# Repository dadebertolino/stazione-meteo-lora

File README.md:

# Stazione meteo LoRa

Stazione meteo scolastica su rete di sensori **LoRa P2P** con moduli **RAK3172**
(firmware RUI3 ≥ 4.1). I nodi trasmettono le misure direttamente a un
ricevitore, senza rete LoRaWAN e senza gateway; il ricevitore le verifica e le
stampa in CSV su seriale; un Raspberry aggiunge data e ora e le invia al sito
della scuola.

**Autore:** [Davide Bertolino](https://www.davidebertolino.it) ·
**Licenze:** software GPL v2 o successive ([`LICENSE`](LICENSE)), hardware
CERN-OHL-S v2 ([`hardware/LICENSE`](hardware/LICENSE))

Il plugin WordPress che mostra i dati sul sito è in un repository a parte,
[dadebertolino/db-stazione-meteo](https://github.com/dadebertolino/db-stazione-meteo),
perché si aggiorna da solo dalle sue release.

```
nodo BME280 (ID 2) ──┐
                     │  LoRa P2P 868,1 MHz        seriale USB, CSV
nodo SHT45 (ID 1)* ──┴───────────────────► ricevitore ──────────────► PC o Raspberry
                                                                       registratore (prove)
                                                                       bridge ──► sito WordPress*
```

\* non ancora realizzati.

| Componente | Ruolo | Stato |
|---|---|---|
| [`nodo_bme280/`](nodo_bme280/nodo_bme280.ino) | nodo temperatura, umidità, pressione con sensore BME280 | firmware 1.2, in prova |
| [`ricevitore_p2p/`](ricevitore_p2p/ricevitore_p2p.ino) | ricevitore: verifica e decodifica i pacchetti, li stampa in CSV | firmware 1.2, in prova |
| [`registratore/`](registratore/registra.py) | salva la seriale del ricevitore con l'ora di arrivo, per le prove | pronto |
| [`test_banco/`](test_banco/esegui.sh) | prove del formato dei pacchetti sul PC, senza schede | 17 test |
| nodo SHT45 | nodo temperatura e umidità | da scrivere quando arrivano i componenti; il ricevitore ne decodifica già il pacchetto |
| [`bridge/`](bridge/README.md) | sul Raspberry: aggiunge data e ora, coda locale, invio al sito | struttura |
| [`hardware/`](hardware/README.md) | progetti KiCad delle schede: nodo BME280 e ricevitore, libreria condivisa | progetti vuoti, scelte da fare |
| [db-stazione-meteo](https://github.com/dadebertolino/db-stazione-meteo) | plugin WordPress: riceve le misure e le mostra sul sito della scuola (repository a parte) | struttura |

Ogni sketch sta in una cartella con lo stesso nome del file `.ino`, come richiede
l'IDE Arduino. Si compilano con il pacchetto di schede RAKwireless RUI3
(verificati con la versione 4.3.0, scheda *WisDuo RAK3172 Evaluation Board*).

**Nodi e ricevitore vanno aggiornati insieme**: il formato dei pacchetti è
cambiato con il firmware 1.0 e il ricevitore scarta quelli del formato
precedente.

## Parametri radio

Devono essere **identici** su nodi e ricevitore. All'avvio ogni sketch fa
un'autodiagnosi: se il modulo è in modalità LoRaWAN passa a P2P e si riavvia, poi
confronta i parametri salvati in flash e corregge quelli diversi. Se il
passaggio a P2P non riesce lo segnala e prosegue, invece di riavviarsi in
continuazione.

| Parametro | Valore |
|---|---|
| Frequenza | 868,100 MHz |
| Spreading factor | SF7 |
| Banda | 125 kHz |
| Coding rate | 4/5 |
| Preambolo | 8 simboli |
| Potenza | 14 dBm |

### Limiti di banda

Con banda 125 kHz centrata su 868,1 MHz il segnale occupa 868,0375-868,1625 MHz,
tutto dentro la sottobanda **868,0-868,6 MHz** (ERC/REC 70-03), che ammette
**25 mW ERP** e **duty cycle 1 %**: al massimo 36 s di trasmissione per ora.

A SF7 il tempo in aria cresce a gradini di 5 simboli (~5 ms). I pacchetti del
formato v1, 15 byte per il BME280 e 13 per l'SHT45, stanno sullo stesso gradino:
**circa 46 ms**.

| Intervallo | Duty cycle |
|---|---|
| 30 s (prova) | ~0,15 % |
| 10 min (esercizio) | ~0,008 % |

Il nodo non compila con un intervallo sotto i 10 s (`static_assert`): con 46 ms
in aria l'1 % ne richiederebbe almeno 4,6.

Fino all'ottobre 2026 la frequenza era 868,000 MHz: metà del segnale cadeva sotto
868,0 MHz, in una banda con duty cycle 0,1 %, superato con l'intervallo di prova.

I 14 dBm sono misurati all'uscita del modulo; il limite di 25 mW è riferito
alla potenza irradiata (ERP) e quindi include il guadagno dell'antenna. Con
un'antenna a stilo o a dipolo si resta nel limite; con un'antenna di guadagno
superiore a ~2 dBi la potenza va ridotta di conseguenza.

868,1 MHz è anche il primo canale di LoRaWAN. Se nella zona ci sono dispositivi
LoRaWAN possono esserci collisioni, visibili come salti nel contatore.

## Nodo BME280

### Alimentazione

**Due stilo AA alcaline** collegate direttamente al pin 3V3 del modulo, senza
regolatore: il RAK3172 funziona fra 2,0 e 3,6 V, e senza regolatore
la tensione di alimentazione del modulo è quella delle
batterie. Il nodo la misura con il riferimento interno dell'STM32WL (VREFINT),
confrontato con la sua taratura di fabbrica.

`api.system.bat.get()` di RUI3 non va usata: nel core 4.3.0
(`service_battery.c`) legge l'ADC solo sul RAK3172-SiP e sulle basi WisBlock;
sul RAK3172 restituisce sempre 3,0 V, ed è il valore fisso che il nodo
trasmetteva fino al firmware 1.1.

| Stato | Tensione (2 × AA) | Per cella |
|---|---|---|
| Nuove | 3,1-3,2 V | 1,55-1,6 V |
| A metà vita | ~2,5 V | ~1,25 V |
| Quasi scariche | ~2,2-2,3 V | ~1,1-1,15 V |
| Spegnimento del modulo | 2,0 V | 1,0 V |

Non usare stilo al litio (tipo Energizer L91): nuove arrivano a circa 3,6 V, al
limite massimo del modulo.

Il nodo trasmette due tensioni: **a riposo**, prima della trasmissione, e
**sotto carico**, misurata a metà della trasmissione. Con le alcaline la
differenza fra le due è il segnale più chiaro di batterie in esaurimento, e al
freddo cresce anche con batterie ancora buone. La tensione sotto carico è quella
della trasmissione *precedente*: quando la misura, il pacchetto è già partito.

All'avvio l'autodiagnosi confronta la tensione con due soglie e segnala un
errore se ne è fuori (solo su seriale, il nodo prosegue):

| Costante | Valore | Significato |
|---|---|---|
| `VBAT_MIN_MV` | 2300 mV | alcaline quasi scariche |
| `VBAT_MAX_MV` | 3600 mV | massimo del RAK3172: sopra si rischia di danneggiarlo |

### Collegamenti I2C

| BME280 | RAK3172 |
|---|---|
| VCC | 3V3 |
| GND | GND |
| SDA | PA11 |
| SCL | PA12 |

Sui moduli a 6 pin, `CSB` va a 3V3 per selezionare l'I2C; `SDO` sceglie
l'indirizzo (a GND = `0x76`, a 3V3 = `0x77`). Lo sketch li prova entrambi e
riconosce un BMP280 montato per errore (niente umidità).

A batteria conviene un modulo **senza regolatore né traslatori di livello**: di
solito sono quelli a 6 pin. I moduli a 4 pin che li hanno consumano sempre,
anche quando il sensore dorme.

### Ciclo di funzionamento

1. Lettura del sensore in *forced mode* (una misura, poi il sensore torna a
   dormire) e della tensione a riposo.
2. Trasmissione del pacchetto; a metà trasmissione, lettura della tensione sotto
   carico per il pacchetto successivo.
3. Sleep per l'intervallo **±10 %, scelto a caso** a ogni ciclo: due nodi accesi
   insieme con lo stesso intervallo, altrimenti, trasmetterebbero sempre nello
   stesso istante e collidrebbero a ogni ciclo. Il seme del generatore casuale
   viene dall'identificativo unico del modulo (DevEUI).

| Costante | Prova | Esercizio |
|---|---|---|
| `INTERVAL_MS` | `30000UL` (30 s ± 3 s) | `600000UL` (10 min ± 1 min) |
| `NODE_DEBUG` | `1`: stampa su seriale | `0`: nessuna stampa |
| `NODE_ID` | 1-15, diverso per ogni nodo | |

Cambiare l'intervallo non richiede modifiche al ricevitore, che ascolta in
continuo.

### Robustezza

| Guasto | Cosa fa il nodo |
|---|---|
| **Sensore che non risponde**, misura non conclusa entro 100 ms, registri ai valori di reset (sensore riavviato) o valori fuori dal campo del BME280 (−40…85 °C, 300…1100 hPa) | sblocca il bus I2C, reinizializza il sensore e lo rilegge subito; se non va ancora trasmette il pacchetto con le misure **non disponibili** e riprova al ciclo successivo |
| **Bus I2C bloccato** (il sensore tiene SDA basso) | 9 impulsi su SCL e una condizione di STOP, poi riapre il bus |
| **Firmware bloccato** | **watchdog** a 8 s: il nodo si riavvia. Il watchdog continua a contare anche in sleep, quindi lo sleep lungo è diviso in tratti di 5 s con una ricarica fra l'uno e l'altro |
| **Sleep interrotto in anticipo** | il tempo si conta con `millis()`, che in RUI3 avanza anche in sleep: il nodo si riaddormenta invece di trasmettere prima del dovuto |
| **Riavvio** (calo di tensione, watchdog, reset) | il primo pacchetto dopo il riavvio ha contatore 0 e porta la causa del reset |

Un nodo con il sensore guasto continua a trasmettere tensioni e contatore: dal
ricevitore si distingue da un nodo spento, che non trasmette nulla.

## Formato dei pacchetti (v1)

Interi **big endian**. Ogni pacchetto finisce con un **CRC-16/CCITT-FALSE**
(polinomio 0x1021, valore iniziale 0xFFFF, controllo su "123456789" = 0x29B1)
calcolato su tutti i byte precedenti.

| Byte | BME280 (15 byte) | SHT45 (13 byte) |
|---|---|---|
| 0 | versione formato (4 bit alti, = 1) · ID nodo (4 bit bassi, 1-15) | uguale |
| 1 | contatore | uguale |
| 2 | tipo di nodo (4 bit alti: 1 = BME280, 2 = SHT45) · causa del reset (4 bit bassi) | uguale |
| 3-4 | temperatura °C × 100, con segno | uguale |
| 5-6 | umidità % × 100 | uguale |
| 7-8 | pressione hPa × 10 | tensione a riposo, mV |
| 9-10 | tensione a riposo, mV | tensione sotto carico, mV |
| 11-12 | tensione sotto carico (trasmissione precedente), mV | CRC-16 |
| 13-14 | CRC-16 | — |

La pressione è quella **misurata sul posto**, non riportata al livello del mare.

### Perché un CRC nel payload

La radio ha già un CRC hardware, attivo, ma in RUI3 4.3.0 un pacchetto che non
lo supera **arriva lo stesso allo sketch**. Il driver radio tratta separatamente
i due eventi che la radio segnala insieme, "pacchetto ricevuto" ed "errore CRC":

1. il payload corrotto viene consegnato alla callback come valido
   (`Status = LORA_P2P_RXDONE`);
2. la callback viene richiamata con `Status = LORA_P2P_RXERROR`, ma con il
   buffer del pacchetto precedente.

Il ricevitore scarta il secondo richiamo guardando `Status`, il primo con il CRC
del payload. Il CRC scarta anche i pacchetti di altri dispositivi che usano gli
stessi parametri radio. Dedotto dai sorgenti del core (`service_lora_p2p.c`,
`radio.c`, `stm32wlxx_hal_subghz.c`) e **confermato sulla scheda** il
25/10/2026: in circa 2 ore e mezza sono arrivati 11 pacchetti estranei da 24
byte (RSSI ~−110 dBm, SNR negativo), ciascuno consegnato prima come ricevuto,
con il payload corrotto, poi come errore radio. Il ricevitore li ha scartati
tutti, 11 per CRC e 11 per `Status`, senza righe duplicate.

### Contatore e riavvii

Il contatore vale **0 solo nel primo pacchetto dopo un riavvio**, poi va da 1 a
255 e riparte da 1. Avanza anche se l'invio fallisce o il sensore è guasto: un
salto vuol dire "pacchetto previsto e non arrivato".

Fra due pacchetti ricevuti dallo stesso nodo i persi sono
`(seq_nuovo − seq_vecchio) mod 255 − 1`, contando sui valori 1-255. A 10 minuti
il contatore fa il giro in circa 42 ore: per silenzi più lunghi si usa l'ora di
arrivo.

Causa del reset, solo nel pacchetto con contatore 0:

| Codice | Causa |
|---|---|
| 1 | accensione o calo di tensione (*brown-out*) |
| 2 | pin NRST (tasto di reset) |
| 3 | software (es. passaggio a P2P dell'autodiagnosi) |
| 4 | watchdog |
| 5 | watchdog a finestra |
| 6 | errore di gestione del basso consumo |
| 7 | altro |

Il microcontrollore non distingue l'accensione da un calo di tensione: lo dice la
tensione nello stesso pacchetto. Con batterie inserite e cariche è
un'accensione; con tensione bassa, o con riavvii ripetuti, è un calo durante la
trasmissione e le batterie sono alla fine.

### Misure non disponibili

Valori riservati, fuori da qualsiasi misura reale:

| Campo | Valore riservato | Quando |
|---|---|---|
| temperatura | `0x8000` | sensore che non risponde |
| umidità, pressione | `0xFFFF` | sensore che non risponde |
| tensione sotto carico | `0xFFFF` | primo pacchetto dopo l'avvio, o trasmissione finita prima della misura |

## Uscita del ricevitore

Seriale a 115200 baud, una riga per pacchetto valido (valori di esempio):

```
# id,seq,tipo,reset,temp_C,ur_pct,press_hPa,vbat_mV,vbat_tx_mV,rssi,snr
# nodo 2: riavvio (causa: alimentazione)
2,0,bme280,1,18.43,61.20,965.3,3091,,-72,9
2,1,bme280,,18.40,61.10,965.2,3090,2987,-71,8
```

- Le misure non disponibili escono come **campi vuoti**; per i nodi SHT45
  `press_hPa` è sempre vuoto.
- `reset` è valorizzato solo con `seq` 0.
- Tutte le altre righe iniziano con `#` e vanno ignorate da chi legge i dati:
  autodiagnosi, avvisi (riavvio di un nodo, sensore guasto), pacchetti scartati
  e, ogni 10 minuti, le statistiche:

```
# stat: 120 validi, 0 CRC errato, 0 errori radio, 0 formato, 0 coda piena, 0 troppo lunghi
```

| Contatore | Significato |
|---|---|
| `CRC errato` | pacchetto corrotto, o di un altro dispositivo |
| `errori radio` | richiami della callback con `Status` di errore (vedi [Perché un CRC](#perché-un-crc-nel-payload)) |
| `formato` | CRC valido ma versione, tipo o lunghezza non riconosciuti |
| `coda piena` | pacchetti arrivati più in fretta di quanto il ricevitore li stampi |
| `troppo lunghi` | oltre 32 byte |

All'accensione il ricevitore stampa un messaggio di benvenuto con la versione
del firmware e aspetta 30 s (`START_WAIT_MS`), con un conto alla rovescia ogni
5 s, prima dell'autodiagnosi e della ricezione.

La callback di ricezione gira nell'interrupt della radio: lì il pacchetto viene
solo copiato in una coda di 7 posti, verifica e stampa avvengono in `loop()`.
Anche il ricevitore ha il watchdog a 8 s, e ogni 10 minuti riavvia la ricezione
per sicurezza.

## Registratore

[`registratore/registra.py`](registratore/registra.py) legge la seriale del
ricevitore e scrive, nella cartella indicata, due file al giorno:

| File | Contenuto |
|---|---|
| `AAAA-MM-GG.log` | tutte le righe, anche quelle `#`, precedute dall'ora di arrivo |
| `AAAA-MM-GG.csv` | solo le righe di dati, con l'ora di arrivo come prima colonna `ricevuto` |

```bash
pip install pyserial
python3 registra.py /dev/ttyUSB0 --cartella registrazioni
```

Su Windows la porta è del tipo `COM5`. Se la porta sparisce (cavo staccato,
ricevitore riavviato) riprova ogni 5 s e registra solo i cambi di stato. Si ferma
con Ctrl+C o `SIGTERM`.

L'ora è quella del computer: **deve essere sincronizzata** (NTP). Senza l'ora di
arrivo i dati delle prove servono a poco.

## Prove

Verifiche fatte al banco, senza schede:

- i due sketch compilano senza avvisi (`--warnings all`), anche con
  `NODE_DEBUG 0`;
- costruzione del pacchetto del nodo e decodifica del ricevitore, estratte dagli
  sketch e compilate sul PC: valori normali e negativi, misure non disponibili,
  avvio con causa del reset, nodo SHT45, alterazione di ciascuno dei 15 byte,
  pacchetto troncato, formato precedente, versione sconosciuta, callback con
  errore, coda piena, priorità delle cause di reset;
- registratore su porta seriale virtuale: righe, file CSV, porta mancante,
  arresto.

Le prove sul formato dei pacchetti si rilanciano dopo ogni modifica agli sketch
(serve un compilatore C++ e python3):

```bash
sh test_banco/esegui.sh
```

Da provare sulle schede:

| Prova | Cosa guardare |
|---|---|
| Avvio del nodo con monitor seriale | autodiagnosi, causa reset "alimentazione", tensione |
| Ricezione a breve distanza | contatore senza salti, `vbat_tx_mV` presente e più bassa di `vbat_mV` |
| Sensore staccato a nodo acceso | righe con campi vuoti; riattaccandolo, le misure tornano senza riavviare |
| Tasto di reset del nodo | `seq` 0, causa 2 |
| Nodo lontano, al limite della portata | contatori `CRC errato` ed `errori radio` nelle statistiche: confermano o smentiscono il doppio richiamo descritto sopra |
| Consumo in sleep, con un multimetro in serie | dà l'autonomia reale; i risvegli ogni 5 s per il watchdog compaiono come brevi picchi |
| Firmware 1.2: multimetro fra 3V3 e GND del nodo | la tensione letta deve coincidere con `vbat_mV` entro qualche decina di mV |
| Alimentatore da banco abbassato piano da 3,2 a 2,0 V | comportamento a batterie scariche: riavvii, causa, tensioni |

## Punti aperti

| Questione | Dettaglio |
|---|---|
| **Tempo della misura sotto carico** | la tensione si legge 20 ms dopo l'avvio della trasmissione, che dura ~46 ms; la lettura con il riferimento interno (5 conversioni dell'ADC) dura circa un millisecondo. Se la trasmissione finisce prima, `vbat_tx_mV` resta vuota |
| **Comportamento a batterie scariche** | oggi il nodo trasmette finché si spegne; si potrebbe allungare l'intervallo sotto una soglia |
| **Bridge** | archivio, allarme sul nodo muto (nessun pacchetto per 2-3 intervalli), pacchetti persi, duplicati e riavvii per nodo |

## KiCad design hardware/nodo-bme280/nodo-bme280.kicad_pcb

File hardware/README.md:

# Hardware

Progetti KiCad delle schede della stazione. Licenza CERN-OHL-S v2
([`LICENSE`](LICENSE)): chi modifica e distribuisce questi progetti deve
pubblicarne i sorgenti con la stessa licenza.

| Scheda | Cartella | Stato |
|---|---|---|
| Nodo BME280: RAK3172, BME280, 2 stilo AA | [`nodo-bme280/`](nodo-bme280/) | schema 0.2 (ERC senza errori), circuito stampato 0.2 per la scatola IP65 da 115 × 90 × 55 mm (DRC senza errori, fori da confermare sulla scatola) |
| Ricevitore USB, per PC o Raspberry Pi | [`ricevitore/`](ricevitore/) | schema 0.2 con USB-B (ERC senza errori, una segnalazione esclusa e motivata), circuito stampato 0.2 (DRC senza errori, da rivedere prima dell'ordine) |
| Nodo SHT45 | — | da progettare quando arrivano i componenti |

## Struttura

```
hardware/
├── librerie/
│   ├── stazione-meteo.kicad_sym    simboli nostri, condivisi dalle schede
│   └── stazione-meteo.pretty/      impronte nostre
├── nodo-bme280/
│   ├── nodo-bme280.kicad_pro
│   ├── nodo-bme280.kicad_sch
│   ├── nodo-bme280.kicad_pcb       circuito stampato
│   ├── nodo-bme280.kicad_dru       regole DRC aggiuntive
│   ├── nodo-bme280-schema.pdf      schema esportato, da rigenerare a ogni modifica
│   ├── sym-lib-table               → librerie/stazione-meteo.kicad_sym
│   └── fp-lib-table                → librerie/stazione-meteo.pretty
└── ricevitore/                     stessa struttura
```

Gli schemi sono in formato **KiCad 9** e si aprono anche con le versioni successive; i circuiti stampati sono in formato **KiCad 10**, quindi serve KiCad 10 o successivo. Ogni progetto trova la libreria condivisa con un percorso relativo (`${KIPRJMOD}/../librerie/`), quindi funziona dovunque si cloni il repository.

**Librerie**: il RAK3172 è nella libreria ufficiale di KiCad, simbolo e impronta (`RF_Module:RAK3172…`). In `librerie/` vanno solo le parti che mancano lì, per esempio la breakout RAK3272S: nessun progetto pubblico ne ha simbolo e impronta.

## Progetti di riferimento

| Progetto | Licenza | Da guardare |
|---|---|---|
| [teapotlaboratories/feather-rak3172](https://github.com/teapotlaboratories/feather-rak3172) | MIT | come si disegna attorno al RAK3172 un circuito a basso consumo: alimentazione, antenna (connettore coassiale), pulsante di reset, connettore SWD, misure di consumo nella documentazione. KiCad 6 |
| [ElektorLabs/lorawan-sensor-node-v2](https://github.com/ElektorLabs/lorawan-sensor-node-v2) | GPL-3.0 | un nodo sensore completo con RAK3172 diviso in fogli gerarchici (RAK3172, sensori, alimentazione), con PDF dello schema e distinta. KiCad 9 |

**Cosa si può riprendere.** Da feather-rak3172 (MIT) si possono copiare parti dello schema o del circuito stampato, citando la fonte e mantenendo l'avviso di licenza MIT. Il progetto Elektor (GPL-3.0) va solo **studiato**: copiarne parti in un progetto CERN-OHL-S metterebbe insieme due licenze reciproche diverse. Le soluzioni che ne prendiamo si ridisegnano da zero.

## Nodo BME280, schema 0.2

| Scelta | Soluzione |
|---|---|
| Modulo radio | RAK3172 saldato, versione con connettore IPEX (`RF_Module:RAK3172`); programmazione da J2 (UART2, BOOT0, NRST) e recupero da J3 (SWD) |
| Sensore | modulo BME280 a 4 pin su connettore femmina J1, nell'ordine VIN, GND, SCL, SDA; I²C su PA12 (SCL) e PA11 (SDA) |
| Batterie | portabatterie 2 × AA Keystone 2462 sulla scheda (BT1), nessun regolatore. In alternativa, dalla 0.2, un portabatterie 2 × AA filato su J4, in parallelo a BT1 e quindi anche lui dietro Q1: se ne monta uno solo |
| Inversione delle batterie | Q1 **DMG2305UX**, P-MOSFET sul positivo (drain verso le batterie, source verso il circuito, gate a massa con R2): VGS(th) da −0,5 a −0,9 V, RDS(on) massima 200 mΩ a VGS = −1,8 V ([datasheet Diodes DS36196 Rev. 8-2](https://www.diodes.com/assets/Datasheets/DMG2305UX.pdf)), quindi meno di 10 mV di caduta a 45 mA anche con le batterie quasi scariche |
| Antenna | connettore u.FL del modulo e cavetto verso SMA a pannello: nessuna pista RF sulla scheda |

Da verificare: codice d'ordine della variante RAK3172 con IPEX; tensione al sensore e consumo a riposo del modulo BME280 a 4 pin (quasi sempre ha un regolatore a 3,3 V, che con le batterie sotto 3,3 V lavora in caduta).

## Nodo BME280, circuito stampato 0.2

| Voce | Valore |
|---|---|
| Scatola | stagna IP65 in ABS da 115 × 90 × 55 mm esterni (LeMotech e altri, su Amazon): dentro circa 105–109 × 80–84 × 45–49 mm secondo il venditore |
| Scheda | 95 × 70 mm, 2 strati, FR4 1,6 mm; fori M3 (H1–H4) a 4 mm dagli angoli |
| Piazzamento | in alto il RAK3172 con J2 (UART2) sopra, J3 (SWD) e J1 (BME280) a sinistra, C1–C3, R1 e RESET a destra; in basso il portabatterie, con Q1 e R2 accanto al polo positivo e J4 sotto di loro. Tutti i componenti sul lato superiore |
| Regole | come il ricevitore: isolamento 0,2 mm, piste 0,25 mm, 0,4 mm per GND, +BATT e BATT_IN, vie 0,6/0,3 mm |
| Massa | il lato inferiore è un piano GND intero: tutte le piste stanno sopra |
| Portabatterie filato | J4: due piazzole per i fili (+ in alto, − in basso), con un foro da 2,2 mm accanto a ciascuna, verso il bordo, da cui far passare il filo prima di saldarlo, così non tira sulla saldatura (`Connector_Wire:SolderWire-0.25sqmm_1x02_P4.2mm_D0.65mm_OD1.7mm_Relief`). Il portabatterie filato si appoggia al posto di BT1 e si blocca con una fascetta fino a 3,6 mm di larghezza nelle asole H5 e H6 (4 × 1,6 mm, non metallizzate), sopra e sotto il corpo di BT1 a metà della sua lunghezza |

**DRC.** Nessuna violazione, nessun collegamento mancante, nessuna differenza dallo schema. `nodo-bme280.kicad_dru` accetta un solo raggio sul lato superiore per le piazzole passanti a GND, che sotto sono collegate con tutti i raggi.

**Prima dell'ordine.**
- Controllare il portabatterie filato: le asole sono a 36 mm di distanza (bordi interni 34,4 mm), pensate per un 2 × AA da circa 57 × 32 mm come BT1. Se è più largo, vanno allontanate.
- Misurare la scatola arrivata: le misure interne e la posizione delle colonnine cambiano da un venditore all'altro. I fori H1–H4 vanno spostati sulle colonnine, oppure la scheda si fissa con distanziali.
- Il BME280 va fuori dalla scatola, in uno schermo antiradiazione, con un cavo a 4 fili da un pressacavo: per un cavo, al posto della femmina a 4 poli in J1 conviene un morsetto a vite o un connettore JST con lo stesso passo.
- Il cavetto u.FL del RAK3172 va al connettore SMA a pannello sulla parete: lasciare spazio sopra il modulo.

## Ricevitore USB, schema 0.2

Una chiavetta che si collega con lo stesso cavo USB al PC o al Raspberry Pi: il sistema la vede come porta seriale, e il bridge funziona com'è.

| Parte | Soluzione |
|---|---|
| Connettore | USB-B femmina a 90°, a foro passante (Jing Extension 921-111A1010D10200, LCSC C46392), cavo A–B come le stampanti. Nella 0.1 era una USB-C (HRO TYPE-C-31-M-12) con R1 e R2 da 5,1 kΩ su CC: tolta perché a passo 0,5 mm è difficile da saldare a mano e da ordinare. La USB-B non ha le linee CC, quindi R1 e R2 non ci sono più; gli altri riferimenti restano com'erano |
| Protezione | USBLC6-2SC6 sulle linee dati |
| Alimentazione | AP2112K-3.3, da VBUS a 3,3 V per modulo e convertitore |
| USB-seriale | CH340C alimentato a 3,3 V (V3 su VCC, come da datasheet): la UART ha già i livelli del RAK3172. DTR e RTS non collegati, perché il bridge (pyserial) li attiva aprendo la porta e non deve resettare il modulo |
| Modulo | RAK3172 con IPEX, antenna su u.FL; seriale su UART2 come ora |
| Programmazione | dalla stessa USB, come adesso con l'adattatore; se il bootloader non risponde: tenere BOOT, premere e rilasciare RESET; oppure SWD su J2 |
| LED | D1 alimentazione; D2 su PA8, da far lampeggiare dal firmware del ricevitore a ogni pacchetto |

**Esclusione ERC.** Il pin V3 del CH340C è definito come uscita di alimentazione (è l'uscita del suo regolatore interno); a 3,3 V il datasheet lo vuole collegato a VCC, quindi sulla stessa rete dell'uscita di U3. L'ERC lo segnala come due uscite collegate: la segnalazione è esclusa, con la motivazione, nel `.kicad_pro`. Le altre regole restano attive.

**Sul Raspberry** il CH340 non ha numero di serie: in `/dev/serial/by-id/` comparirà con un nome come `usb-1a86_USB_Serial-if00-port0`, da verificare con `ls /dev/serial/by-id/` e da rimettere nel `config.toml` del bridge al posto di quello dell'adattatore FTDI.

## Ricevitore USB, circuito stampato 0.2

| Voce | Valore |
|---|---|
| Scheda | 60 × 25 mm, 2 strati, FR4 1,6 mm |
| Piazzamento | USB-B sul bordo sinistro, che sporge di circa 8 mm come sull'Arduino Uno: sulla scheda restano 9 mm di corpo e le linguette dello schermo, a 2,5 mm dal bordo; poi USBLC6 e regolatore, CH340C, RAK3172 al centro; a destra RESET (SW1), SWD (J2) e BOOT (SW2); LED in basso. Tutti i componenti sul lato superiore |
| Regole | isolamento 0,2 mm; piste 0,25 mm, 0,4 mm per VBUS, +3V3 e GND (classe `Alimentazione`); vie 0,6/0,3 mm: nei limiti standard di JLCPCB e PCBWay |
| Massa | piano GND su tutti e due gli strati; il lato inferiore è quasi intero (46 mm di piste in tutto) e ogni piazzola GND vi arriva con una via |
| Sbroglio | [Freerouting](https://github.com/freerouting/freerouting) 1.9.0 da un'esportazione Specctra per la 0.1; nella 0.2 VBUS, D+ e D− attorno alla USB-B sono tracciati a mano. Ogni volta controllo DRC con confronto sullo schema |

**DRC.** Nessun errore, nessun collegamento mancante, nessuna differenza dallo schema. Restano due avvisi di serigrafia tagliata dal bordo: sono le linee del corpo della USB-B, che sporge dal bordo. In `ricevitore.kicad_dru` c'è una regola sola: i piedini GND dei pulsanti hanno un solo raggio verso il piano superiore, perché sul lato inferiore il piano li raggiunge con tutti i raggi.

**Da guardare prima dell'ordine.**
- Le linee USB D+ e D− passano sul lato inferiore dalla USB-B fino a U2 (e D+ fino a U4), sotto la pista di VBUS: a 12 Mbit/s non serve l'impedenza controllata, ma conviene che siano corte e vicine.
- Sotto il RAK3172 ci sono due vie di massa (vicino ai pin 11 e 17): le vie sono coperte dal solder mask su tutti e due i lati, ma se il fondo del modulo ha parti scoperte vanno spostate.
- Nessun foro di fissaggio: dipende dal contenitore.

## File per la produzione

In ogni cartella delle schede, generati con KiCad 10.0.7 dal `.kicad_pcb` e da rigenerare a ogni modifica:

| File | Contenuto |
|---|---|
| `gerber/` e `<scheda>-gerber-0.2.zip` | rame, solder mask e serigrafia dei due lati, pasta superiore, contorno; foratura Excellon in mm, fori metallizzati e no nello stesso file |
| `<scheda>-bom-jlcpcb.csv` | distinta per il montaggio JLCPCB, solo SMD, con i codici LCSC; senza il RAK3172 |
| `<scheda>-cpl-jlcpcb.csv` | posizioni e rotazioni degli SMD, lato superiore |

JLCPCB monta solo gli SMD: i passanti (pulsanti, pin header, USB-B del ricevitore, femmina del BME280, portabatterie) farebbero salire molto il costo del montaggio e si saldano a mano, come il RAK3172-8-SM-I (C19723904), che a fine ottobre 2026 è esaurito su LCSC. Le rotazioni di U2, U3, U4 e Q1 sono corrette rispetto a KiCad per i modelli di JLCPCB, da ricontrollare comunque nell'anteprima. I Gerber del nodo vanno rifatti dopo aver spostato i fori sulle colonnine della scatola.

**Stencil unico.** `stencil-nodo-ricevitore-F_Paste.gtp` (e lo zip `stencil-nodo-ricevitore-0.2.zip`, con il ricevitore 0.2) mette in un solo Gerber, senza contorno, le paste superiori delle due schede: il nodo nella sua posizione, il ricevitore 75 mm più in basso, 5 mm sotto il bordo del nodo. Le aperture del ricevitore sono rinumerate da D110. Si rigenera dalle due `F_Paste` dopo ogni modifica delle schede.

## Scelte ancora aperte

| Domanda | Possibilità |
|---|---|
| Contenitore | misure del contenitore stagno e dello schermo per il sensore: decidono la forma della scheda del nodo |

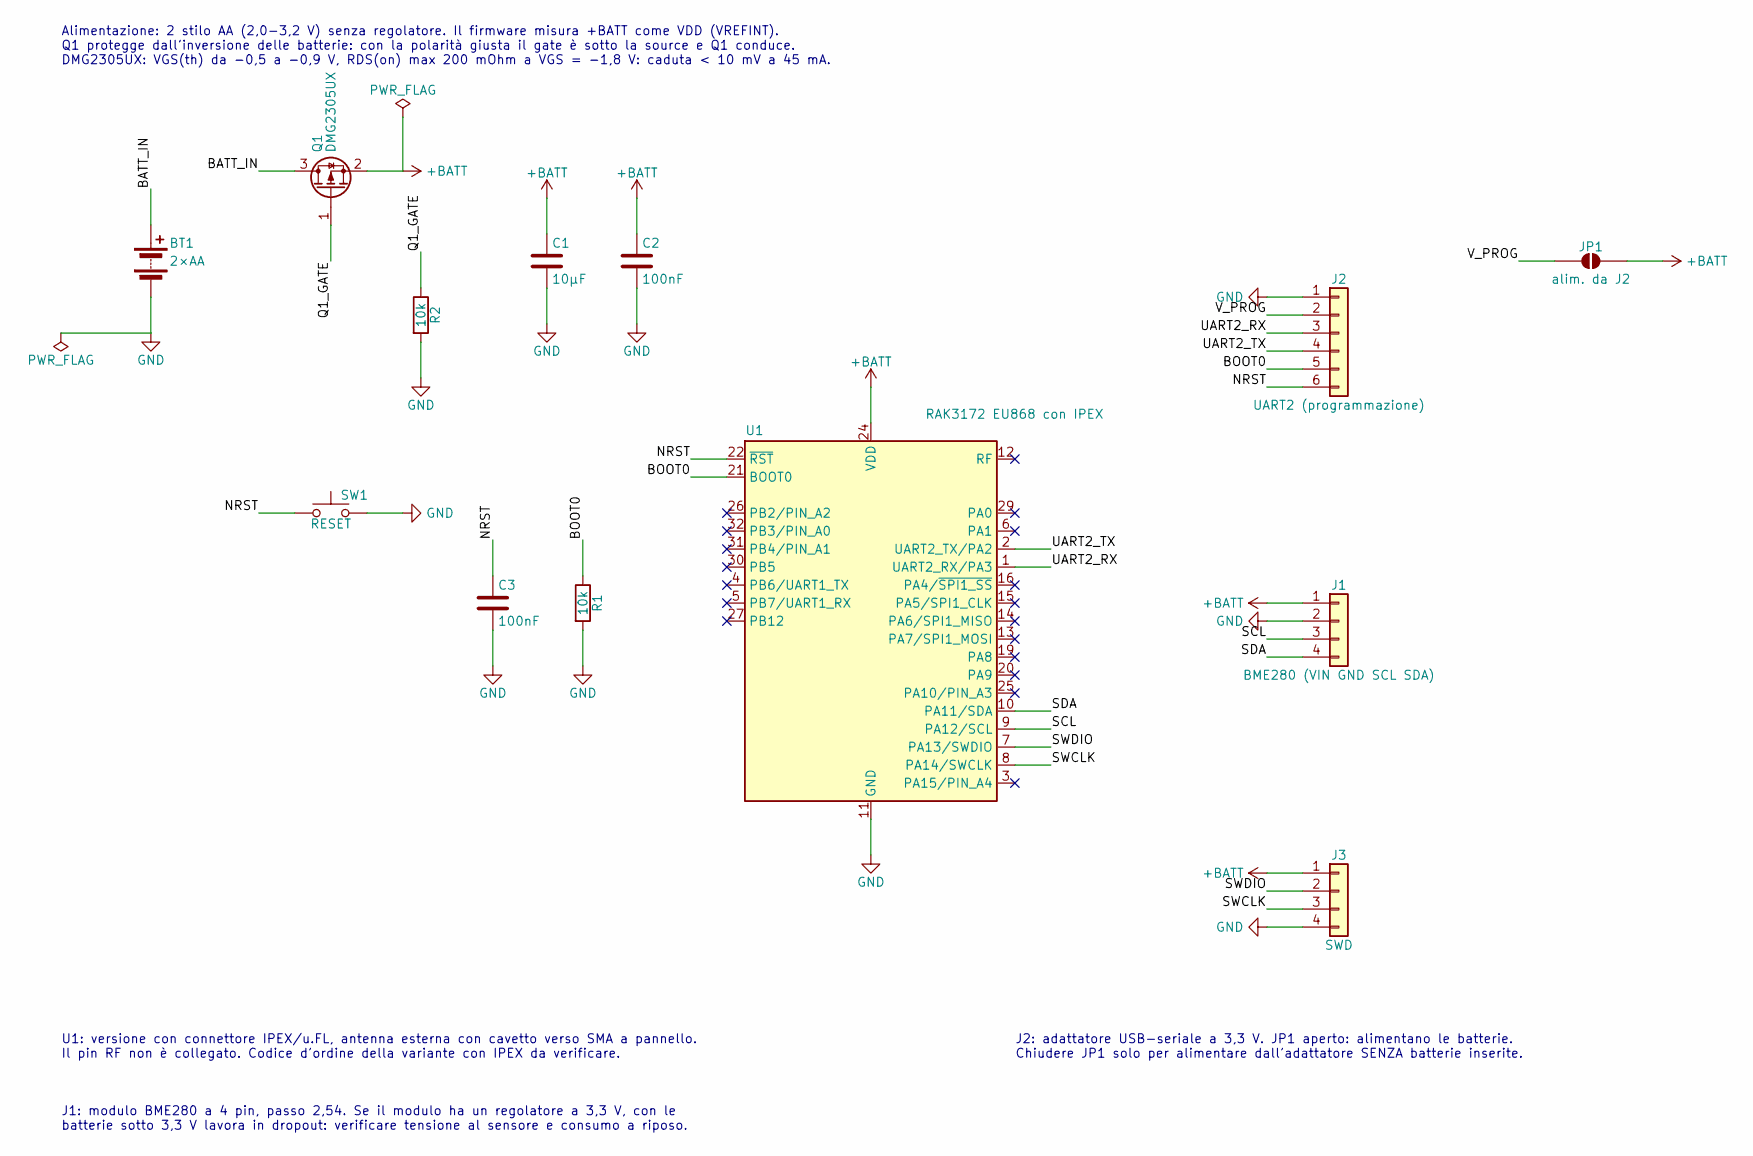
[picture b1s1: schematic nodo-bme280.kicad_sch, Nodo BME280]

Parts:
BT1: 2×AA; BatteryHolder_Keystone_2462_2xAA
C1: 10µF; C_0805_2012Metric_Pad1.18x1.45mm_HandSolder
C2, C3: 100nF; C_0805_2012Metric_Pad1.18x1.45mm_HandSolder
J1: BME280 (VIN GND SCL SDA); PinSocket_1x04_P2.54mm_Vertical
J2: UART2 (programmazione); PinHeader_1x06_P2.54mm_Vertical
J3: SWD; PinHeader_1x04_P2.54mm_Vertical
JP1: alim. da J2; SolderJumper-2_P1.3mm_Open_RoundedPad1.0x1.5mm
Q1: DMG2305UX; SOT-23_Handsoldering
R1, R2: 10k; R_0805_2012Metric_Pad1.20x1.40mm_HandSolder
SW1: RESET; SW_PUSH_6mm
U1: RAK3172 EU868 con IPEX; RAK3172

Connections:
+BATT: C1.1, C2.1, J1.1, J3.1, JP1.2 (B), Q1.2 (S), U1.24 (VDD)
/BATT_IN: BT1.1 (+), Q1.3 (D); also elsewhere on the board
/BOOT0: J2.5, R1.1, U1.21 (BOOT0)
/NRST: C3.1, J2.6, SW1.1, U1.22 (~RST)
/Q1_GATE: Q1.1 (G), R2.1
/SCL: J1.3, U1.9 (PA12/SCL)
/SDA: J1.4, U1.10 (PA11/SDA)
/SWCLK: J3.3, U1.8 (PA14/SWCLK)
/SWDIO: J3.2, U1.7 (PA13/SWDIO)
/UART2_RX: J2.3, U1.1 (UART2_RX/PA3)
/UART2_TX: J2.4, U1.2 (UART2_TX/PA2)
/V_PROG: J2.2, JP1.1 (A)
GND: BT1.2 (-), C1.2, C2.2, C3.2, J1.2, J2.1, J3.4, R1.2, R2.2, SW1.2, U1.11 (GND), U1.17 (GND), U1.18 (GND), U1.23 (GND), U1.28 (GND); also elsewhere on the board

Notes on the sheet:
Alimentazione: 2 stilo AA (2,0-3,2 V) senza regolatore. Il firmware misura +BATT come VDD (VREFINT). Q1 protegge dall'inversione delle batterie: con la polarità giusta il gate è sotto la source e Q1 conduce. DMG2305UX: VGS(th) da -0,5 a -0,9 V, RDS(on) max 200 mOhm a VGS = -1,8 V: caduta < 10 mV a 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
U1: versione con connettore IPEX/u.FL, antenna esterna con cavetto verso SMA a pannello. Il pin RF non è collegato. Codice d'ordine della variante con IPEX da verificare.
J1: modulo BME280 a 4 pin, passo 2,54. Se il modulo ha un regolatore a 3,3 V, con le batterie sotto 3,3 V lavora in dropout: verificare tensione al sensore e consumo a riposo.
J2: adattatore USB-seriale a 3,3 V. JP1 aperto: alimentano le batterie. Chiudere JP1 solo per alimentare dall'adattatore SENZA batterie inserite.

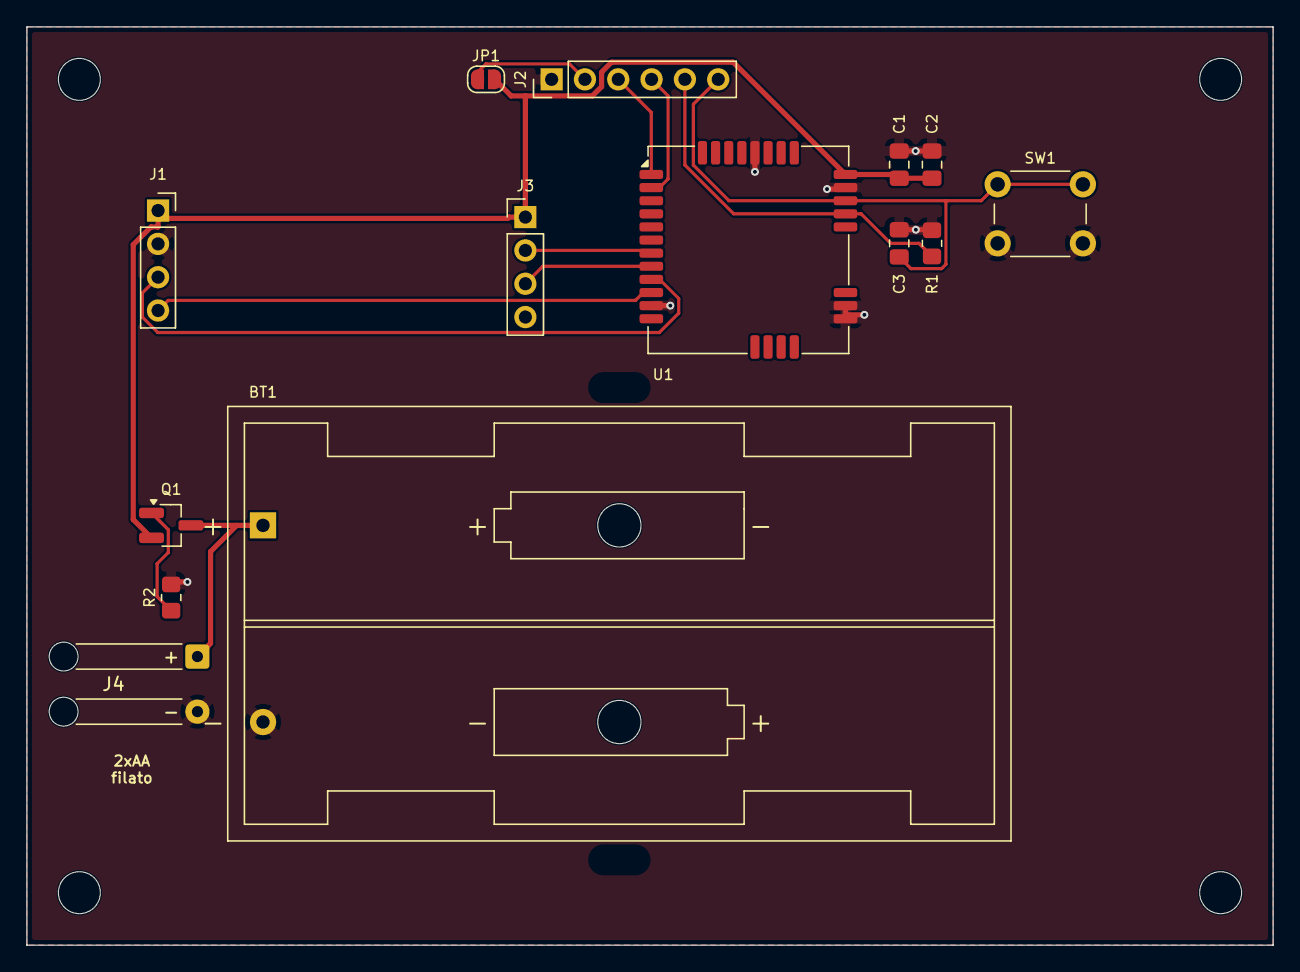
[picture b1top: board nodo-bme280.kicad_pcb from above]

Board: 2 copper layers, 95.0 x 70.0 mm, 20 parts (0 on the bottom side), 13 nets.

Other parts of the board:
H1, H2, H3, H4: M3; MountingHole_3.2mm_M3
H5, H6: Asola fascetta; Asola_fascetta_4x1.6mm
J4: Portabatterie filato; SolderWire-0.25sqmm_1x02_P4.2mm_D0.65mm_OD1.7mm_Relief

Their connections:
/BATT_IN: J4.1; also elsewhere on the board
GND: J4.2; also elsewhere on the board

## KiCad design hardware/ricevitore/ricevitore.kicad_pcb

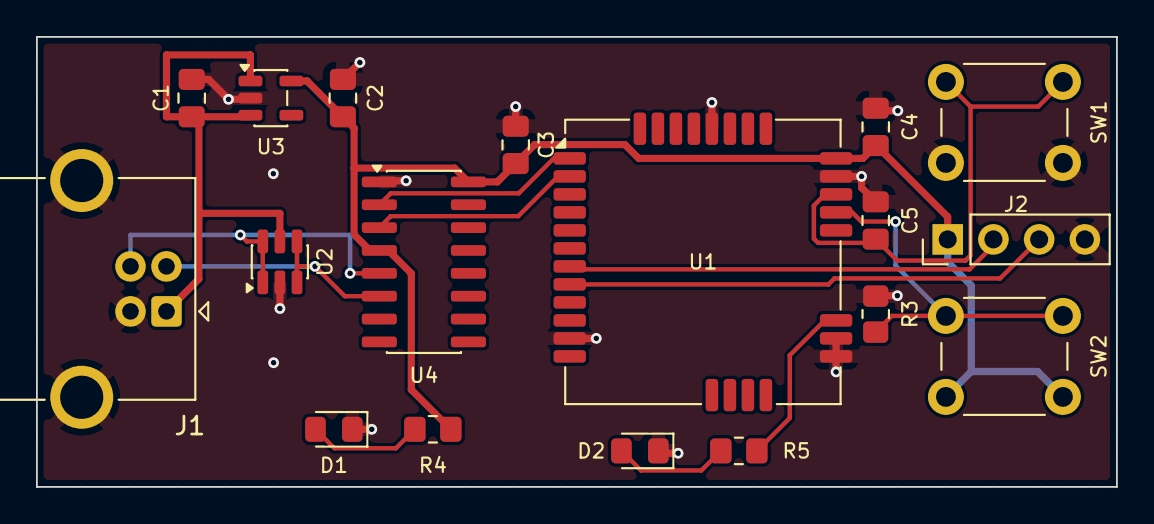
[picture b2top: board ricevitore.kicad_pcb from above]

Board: 2 copper layers, 60.0 x 25.0 mm, 18 parts (0 on the bottom side), 14 nets.

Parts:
C1: 1µF; C_0805_2012Metric_Pad1.18x1.45mm_HandSolder
C2: 10µF; C_0805_2012Metric_Pad1.18x1.45mm_HandSolder
C3, C4, C5: 100nF; C_0805_2012Metric_Pad1.18x1.45mm_HandSolder
D1: verde; LED_0805_2012Metric_Pad1.15x1.40mm_HandSolder
D2: giallo; LED_0805_2012Metric_Pad1.15x1.40mm_HandSolder
J1: USB-B; USB_B_Jing_921-111A1010D10200_Horizontal
J2: SWD; PinHeader_1x04_P2.54mm_Vertical
R3: 10k; R_0805_2012Metric_Pad1.20x1.40mm_HandSolder
R4, R5: 1k; R_0805_2012Metric_Pad1.20x1.40mm_HandSolder
SW1: RESET; SW_PUSH_6mm
SW2: BOOT; SW_PUSH_6mm
U1: RAK3172 EU868 con IPEX; RAK3172
U2: USBLC6-2SC6; SOT-23-6
U3: AP2112K-3.3; SOT-23-5
U4: CH340C; SOIC-16_3.9x9.9mm_P1.27mm

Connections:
+3V3: C2.1, C3.1, C4.1, J2.1, R4.1, SW2.2, U1.24, U3.5, U4.4, U4.16
/BOOT0: R3.1, SW2.1, U1.21
/LED_PWR_A: D1.2, R4.2
/LED_RX: R5.1, U1.19
/LED_RX_A: D2.2, R5.2
/NRST: C5.1, SW1.1, U1.22
/SWCLK: J2.3, U1.8
/SWDIO: J2.2, U1.7
/UART2_RX: U1.1, U4.2
/UART2_TX: U1.2, U4.3
/USB_DM: J1.2, U2.3, U2.4, U4.6
/USB_DP: J1.3, U2.1, U2.6, U4.5
GND: C1.2, C2.2, C3.2, C4.2, C5.2, D1.1, D2.1, J1.4, J1.SH, J2.4, R3.2, SW1.2, U1.11, U1.17, U1.18, U1.23, U1.28, U2.2, U3.2, U4.1
VBUS: C1.1, J1.1, U2.5, U3.1, U3.3

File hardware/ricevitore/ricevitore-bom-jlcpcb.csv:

Comment,Designator,Footprint,LCSC Part #
1µF 50V X7R 0805,C1,C_0805_2012Metric_Pad1.18x1.45mm_HandSolder,C28323
10µF 25V X5R 0805,C2,C_0805_2012Metric_Pad1.18x1.45mm_HandSolder,C15850
100nF 50V X7R 0805,"C3,C4,C5",C_0805_2012Metric_Pad1.18x1.45mm_HandSolder,C49678
LED verde 0805 KT-0805G,D1,LED_0805_2012Metric_Pad1.15x1.40mm_HandSolder,C2297
LED giallo 0805 KT-0805Y,D2,LED_0805_2012Metric_Pad1.15x1.40mm_HandSolder,C2296
10k 1% 0805,R3,R_0805_2012Metric_Pad1.20x1.40mm_HandSolder,C17414
1k 1% 0805,"R4,R5",R_0805_2012Metric_Pad1.20x1.40mm_HandSolder,C17513
USBLC6-2SC6,U2,SOT-23-6,C7519
AP2112K-3.3TRG1,U3,SOT-23-5,C51118
CH340C,U4,SOIC-16_3.9x9.9mm_P1.27mm,C84681
